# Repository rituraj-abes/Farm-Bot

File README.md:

# Farm Bot Remote Control PCB

This repository contains the design files and documentation for a PCB created to control a Farm Bot vehicle. The PCB was designed for Funeda Pvt. Ltd. using EAGLE software, and the housing box for the remote was created using LaserCAD software.

## Project Overview

The Farm Bot Remote Control PCB is a custom-designed printed circuit board intended to facilitate the control of a Farm Bot vehicle. This remote control allows for efficient and precise management of the bot's movements and operations, enhancing agricultural automation.

## Features

- **Remote Control**: Designed to provide reliable control over the Farm Bot vehicle.
- **Custom PCB**: Created using EAGLE software to ensure optimal performance and functionality.
- **Laser-Cut Housing**: The remote's box is designed using LaserCAD software, providing a robust and precise enclosure.

## Software Used

- **EAGLE**: For designing the PCB layout and schematics.
- **LaserCAD**: For designing the housing box for the remote control.

## Files in This Repository

- `FarmBot.brd`: Contains the EAGLE design files for the PCB.
- `FarmBot.sch`: Includes the circuit schematics for the PCB.
- `05 schematic.png`: Image of the circuit schematic for quick reference.

## Getting Started

### Prerequisites

- EAGLE software to view and edit the PCB design files.
- LaserCAD software to view and edit the housing design files.

### Instructions

1. **PCB Design**: Open the EAGLE design files to view and modify the PCB layout and schematics.
2. **Housing Design**: Open the LaserCAD files to view and modify the remote's housing box design.

## Schematic

## Usage

Once assembled, the remote can be used to control the Farm Bot vehicle. Ensure that all connections are properly made and tested before deploying in the field.

## Contributing

Contributions are welcome! If you have any suggestions or improvements, please create an issue or submit a pull request.

## Acknowledgements

- Thanks to the teams behind EAGLE and LaserCAD for their powerful design software.
- Special thanks to Funeda Pvt. Ltd. for their support and collaboration.

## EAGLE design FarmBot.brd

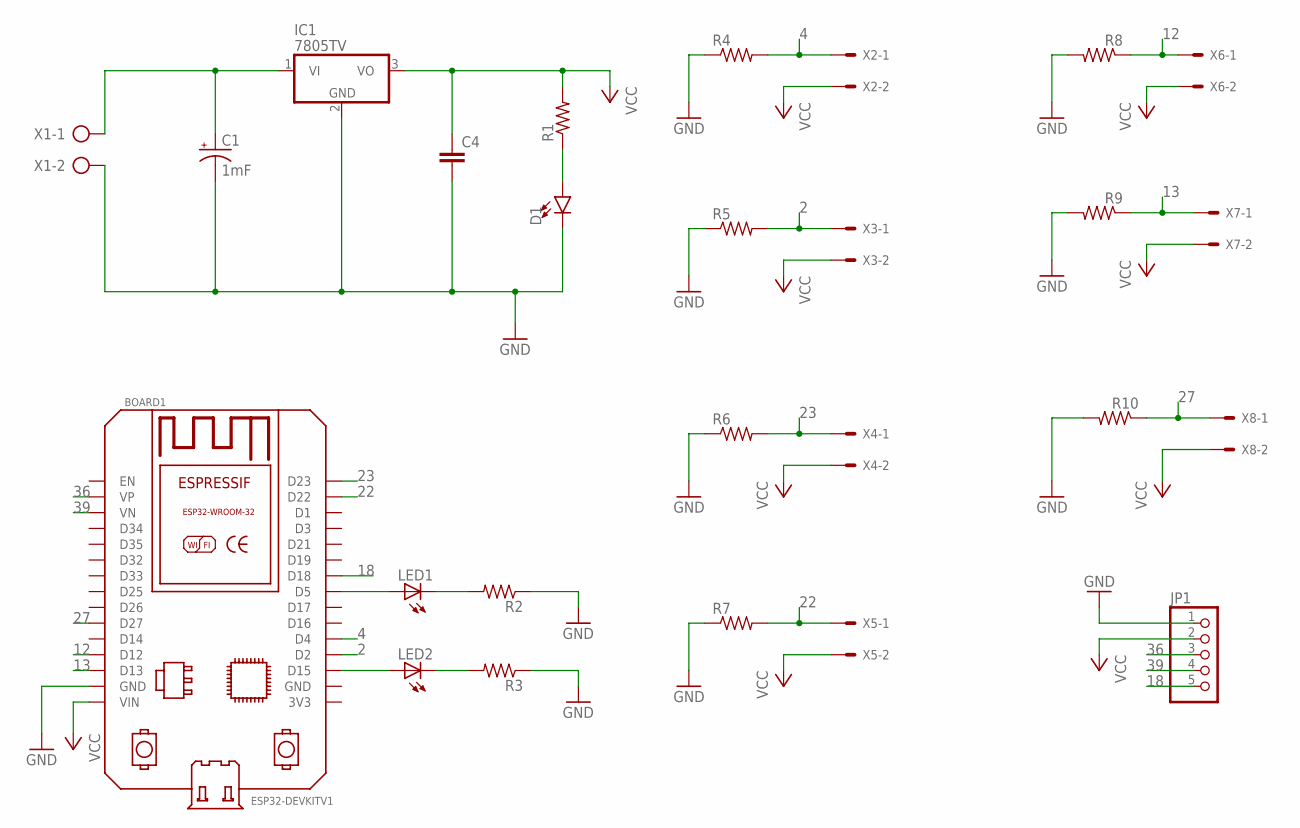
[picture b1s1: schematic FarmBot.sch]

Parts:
BOARD1: ESP32DEVKITV1; ESP32-DEVKITV1
C1: 1mF; CPOL-RADIAL-5MM-10MM
C4: C2,5-3; C2.5-3
D1: LED3MM; LED_3MM
IC1: 7805TV; TO220V
JP1: PINHD-1X5; 1X05
LED1, LED2: LED3MM
R1, R2, R3: R-US_0204/7; 0204/7
R4, R5, R6, R7, R8, R9, R10: R-US_0207/9; 0207/9
X1: AK500/2-H
X2, X3, X4, X5, X6, X7, X8: KK-156-2

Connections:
2: BOARD1.D2, R5.2, X3.1
4: BOARD1.D4, R4.2, X2.1
12: BOARD1.D12, R8.1, X6.1
13: BOARD1.D13, R9.1, X7.1
18: BOARD1.D18, JP1.5
22: BOARD1.D22, R7.2, X5.1
23: BOARD1.D23, R6.2, X4.1
27: BOARD1.D27, R10.1, X8.1
36: BOARD1.VP, JP1.3
39: BOARD1.VN, JP1.4
GND: BOARD1.GND, C1.-, C4.2, D1.K (C), IC1.2 (GND), JP1.1, R2.1, R3.1, R4.1, R5.1, R6.1, R7.1, R8.2, R9.2, R10.2, X1.2
unnamed: C1.+, IC1.1 (VI), X1.1
unnamed: BOARD1.D5, LED1.A
unnamed: BOARD1.D15, LED2.A
unnamed: LED1.K (C), R2.2
unnamed: D1.A, R1.1
unnamed: LED2.K (C), R3.2
VCC: BOARD1.VIN, C4.1, IC1.3 (VO), JP1.2, R1.2, X2.2, X3.2, X4.2, X5.2, X6.2, X7.2, X8.2

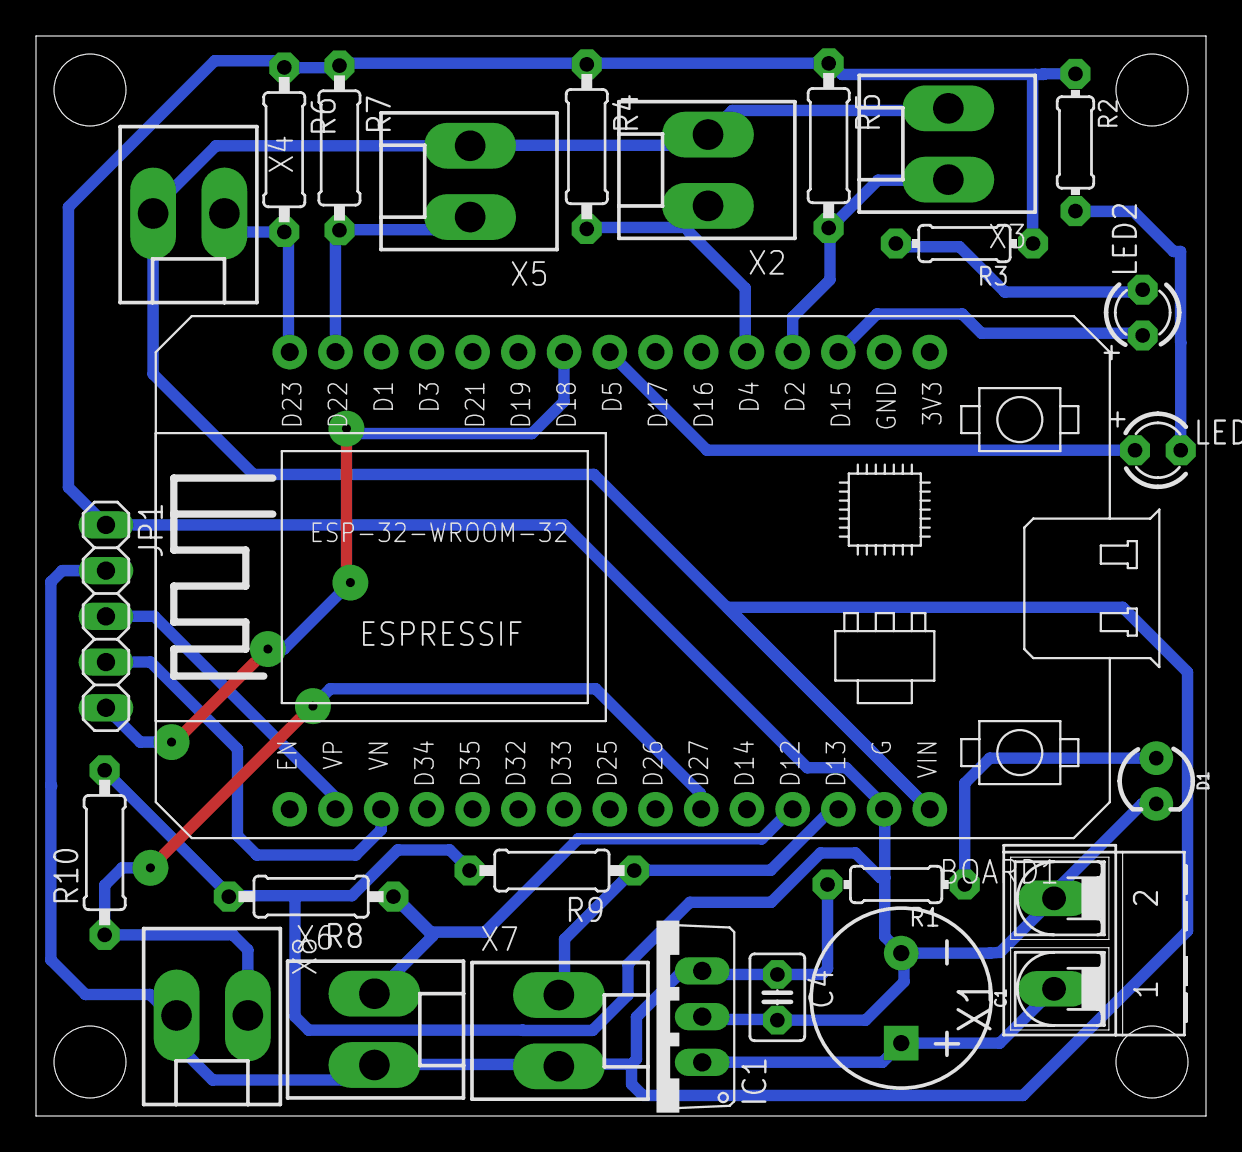
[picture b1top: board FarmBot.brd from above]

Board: 2 copper layers, 65.0 x 60.0 mm, 26 parts (0 on the bottom side), 18 nets.

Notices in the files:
parts and their libraries:
SparkFun-Capacitors: Licensing: Creative Commons ShareAlike 4.0 International - https://creativecommons.org/licenses/by-sa/4.0
